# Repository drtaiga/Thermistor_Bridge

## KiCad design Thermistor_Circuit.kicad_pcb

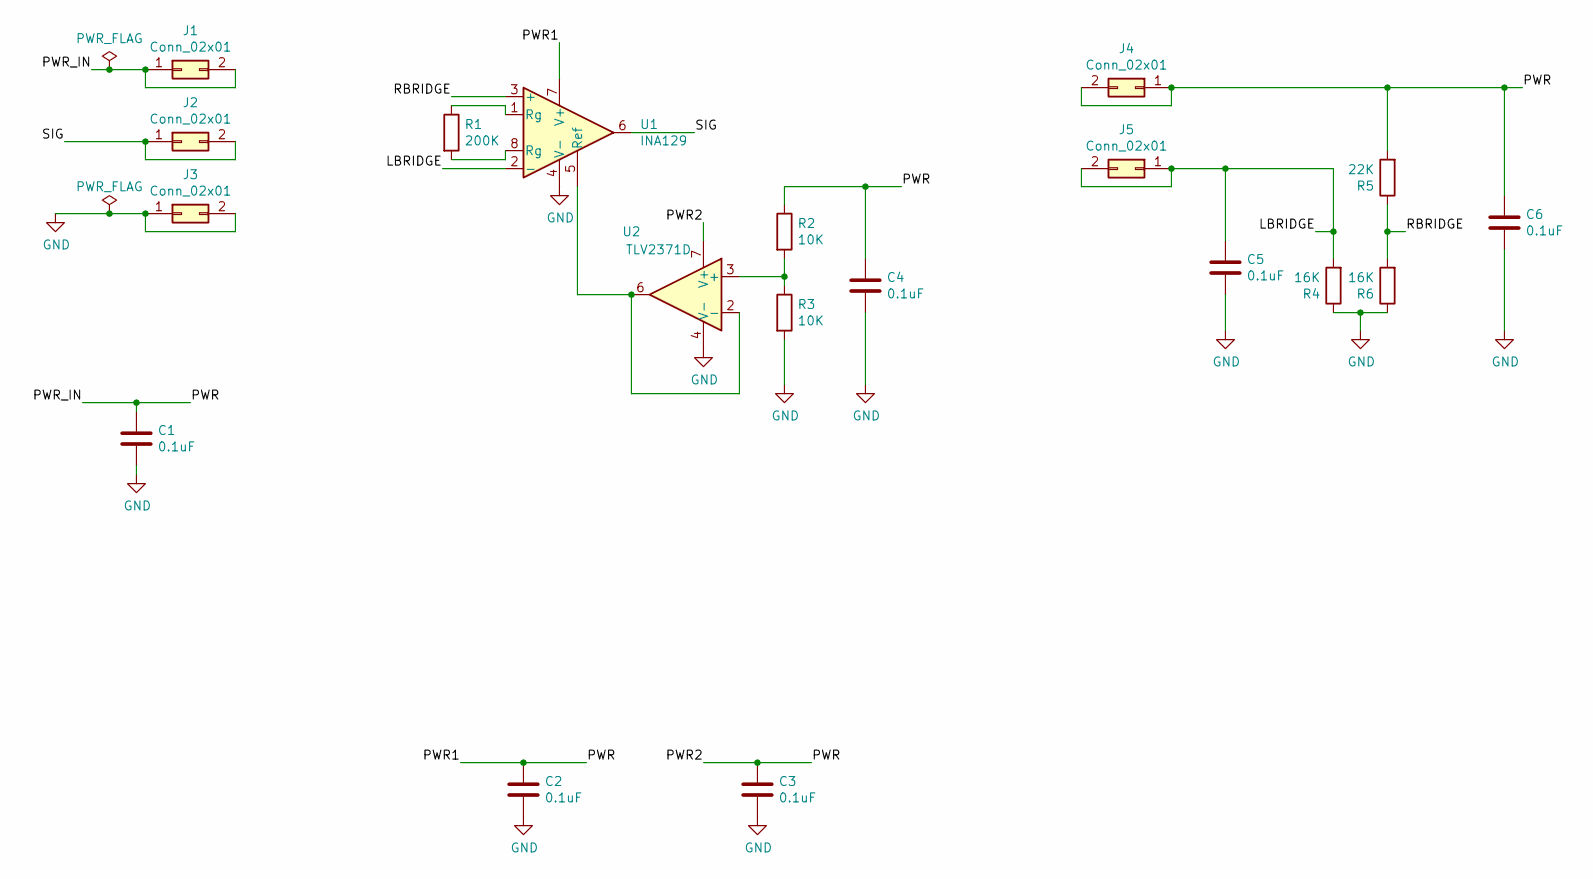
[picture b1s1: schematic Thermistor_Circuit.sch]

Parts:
C1, C2, C3, C4, C5, C6: 0.1uF; C_0805_2012Metric_Pad1.18x1.45mm_HandSolder
J1, J2, J3, J4, J5: Conn_02x01; Molex_SoderRight_02x01
R1: 200K; R_0805_2012Metric_Pad1.20x1.40mm_HandSolder
R2, R3: 10K; R_0805_2012Metric_Pad1.20x1.40mm_HandSolder
R4, R6: 16K; R_0805_2012Metric_Pad1.20x1.40mm_HandSolder
R5: 22K; R_0805_2012Metric_Pad1.20x1.40mm_HandSolder
U1: INA129; SOIC-8_3.9x4.9mm_P1.27mm
U2: TLV2371D; SOIC-8_3.9x4.9mm_P1.27mm

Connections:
/LBRIDGE: C5.2, J5.1, J5.2, R4.2, U1.2 (-)
/PWR: C1.1, C2.1, C3.1, C4.1, C6.1, J1.1, J1.2, J4.1, J4.2, R2.1, R5.2, U1.7 (V+), U2.7 (V+)
/RBRIDGE: R5.1, R6.2, U1.3 (+)
/SIG: J2.1, J2.2, U1.6
GND: C1.2, C2.2, C3.2, C4.2, C5.1, C6.2, J3.1, J3.2, R3.2, R4.1, R6.1, U1.4 (V-), U2.4 (V-)
unnamed: R1.1, U1.1 (Rg)
unnamed: R1.2, U1.8 (Rg)
unnamed: R2.2, R3.1, U2.3 (+)
unnamed: U1.5 (Ref), U2.2 (-), U2.6

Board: 2 copper layers, 19 parts (8 on the bottom side), 9 nets, no tracks yet.

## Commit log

2020-11-30 Initial commit of KiCad files
2020-12-01 adding thermistor notebook
2020-12-07 Modified notebook interactive graphs
2020-12-11 Added Binder info
